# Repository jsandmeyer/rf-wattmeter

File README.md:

## Wattmeter

Based on AK3Y's wattmeter published in QSL magazine.

See license in `main.cpp` for code.  Some other files (like the font) are licensed separately.

### Differences from previous designs
1. Built to run upside-down (heatsink up)
2. Changed to use a Pi Pico 2 to reduce BOM cost
3. Added some built-in standoffs to case
4. Added new holes for USB, and for optional PowerPoles
5. Changed dimensions of PCB and drill/tap locations for heatsink
6. Used 128x64 OLED from AliExpress which did not match datasheet / original dimensions at all
7. Changed microstrip width based on recommendation from calculator
8. I used connectors for everything, but you could just solder the wires in
9. Changed other dimensions of case cutouts
10. Used mostly different parts from original design

### Printing
Try to orient the parts so the smooth side faces out.
1. Print bottom shell normally.
2. The top shell should be rotated 180 degrees for better printing.
3. Front and back panels should be oriented so the "outside" of each plate faces the build plate for a smooth finish.

### Assembly

#### Parts Required

| ID      | Description                   | QTY | Optional QTY |
|---------|-------------------------------|-----|--------------|
| PCB1    | RF PCB                        | 1   |              |
| PCB2    | Pico PCB                      | 1   |              |
| A1      | Raspberry Pi Pico 2           | 1   |              |
| A2      | SSD1306 128x64 I2C OLED       | 1   |              |
| C1      | 10nF 1206 Cer. Cap.           | 1   |              |
| C2      | 1nF 1206 Cer. Cap.            | 1   |              |
| C3      | 10uF 35V 5mm Elec. Cap.       |     | 1            |
| C4      | 47uF 35V 5mm Elec. Cap.       |     | 1            |
| D1-2a,b | TMMBAT41FILM 100V Diode       | 3   |              |
| D3      | PBZTBR13.0B Zener Diode       | 1   |              |
| D4      | 1N5819                        |     | 1            |
| HS1     | 60x45x18mm heatsink           | 1   |              |
| J1      | SMA board-edge connector      | 1   |              |
| J2      | JST-XA BM02B-XASS-TF          | 1   |              |
| J3-4    | JST-XA B02B-XASK-1            | 1   | 1            |
| J5      | 1x4 2.54mm Breakaway Hdr.     | 1   |              |
| R1      | RFR 50-250 Flange Resistor    | 1   |              |
| R2      | 100K 1206 Resistor            | 1   |              |
| R3      | 3K 1206 Resistor              | 1   |              |
| R4      | DNP                           |     |              |
| TH1     | DNP                           |     |              |
| U1      | UA7805                        |     | 1            |
| VR1     | 100K PT10WV05-104A2020-3-NE-S | 1   |              |

#### Cable Assemblies
Cable assemblies assume Pin 1 of a connector is the RIGHTMOST contact if you are looking at the connector's contact end, with the latch facing UP.
Cut wires to the length indicated, then strip and crimp them.

1. 5" Inter-PCB Wire
   1. JST-XA connectors
   2. RF PCB side: Pin 1 is red, Pin 2 is black
   3. Pico PCB side: Pin 1 is black, Pin 2 is red
   4. Pins 1 and 2 are reversed on either board
2. 2.5" PowerPole Wire (optional)
   1. JST-XA connector and PowerPole connector
   2. Pico PCB side: Pin 1 is red, Pin 2 is black
3. 3.5" OLED Wire (DuPont/Molex)
   1. Connectors are symmetrical
   2. Try to use a marked or black conductor for GND

#### Tools Needed
1. Crimping tool for JST & DuPont connectors
2. Crimping tool for PowerPole connectors
3. Drill bits and taps for M2 and M3 screw holes
4. Wire cutters, strippers, pliers
5. Metric allen key / screwdriver / wrench / socket for M2/3 screws and nuts
6. Soldering iron with solder, flux, and solder-wick
7. 3D printer if printing your own case

#### Steps
1. Assemble the heatsink, RF PCB, and flange resistor prior to soldering anything.
   1. Use 4x 6mm M3 screws to hold the PCB to the heatsink
   2. Use 2x 6mm M2 screws to hold the flange resistor to the heatsink
   3. Make sure the flange resistor tab rests on/above the PCB pad for it
2. Soldering the RF PCB
   1. Use flux liberally
   2. The pads for diodes were designed for larger diodes, but many will fit fine
3. Soldering the Pico PCB
   1. Parts U1, C3, C4, D4, and J4 may be omitted if you do not want an external power supply other than USB
   2. D4 is a very tight fit
   3. Use flux to help solder the Pico 2
   4. R4 and Thermistor are optional in case you want to have a Thermistor (you will need to code this in)
4. Installing the PCBs
   1. Insert 4x 8mm M3 screws into the screw holes on the "top" shell from the outside
   2. Place the RF PCB into the "top" shell with the heatsink going through the big hole, and the SMA adapter through the small side hole, aligned with the M3 screws
   3. Attach 4x 15mm~6mm M3 hex standoffs (female side) to the M3 screws to hold the RF PCB down
   4. Attach one end of the inter-PCB wire to the RF PCB
   5. Place the Pico PCB onto the M3 hex standoffs (male side) so that the potentiometer and BOOTSEL button align to the holes when the "bottom" shell is placed onto the "top" shell
   6. Use 4x M3 lock nuts to hold the Pico PCB to the M3 standoffs
   7. Attach the other end of the inter-PCB wire to the Pico PCB
5. Assembling the OLED panel
   1. Mark on the top edge of the OLED panel above the GND pin
   2. Use 4x 8mm M2 screws and M2 lock nuts to hold the OLED display in place on the front panel - be gentle with the PCB
   3. Place the OLED display panel so the connector is above the Pico PCB
   4. Attach the OLED wire between the display and the PCB
6. Assembling the Power/USB panel
   1. Install the PowerPole connector
   2. File the hole for the PowerPole connector if needed
   3. Use glue to secure the PowerPole connector if desired
   4. Place the Power/USB panel so the PowerPole connector is above the Pico PCB
   5. Attach the PowerPole wire to the PCB
7. Assemble the top of the case
   1. Place the "bottom" shell on the assembly
   2. Affix with 4x 6mm M2 screws

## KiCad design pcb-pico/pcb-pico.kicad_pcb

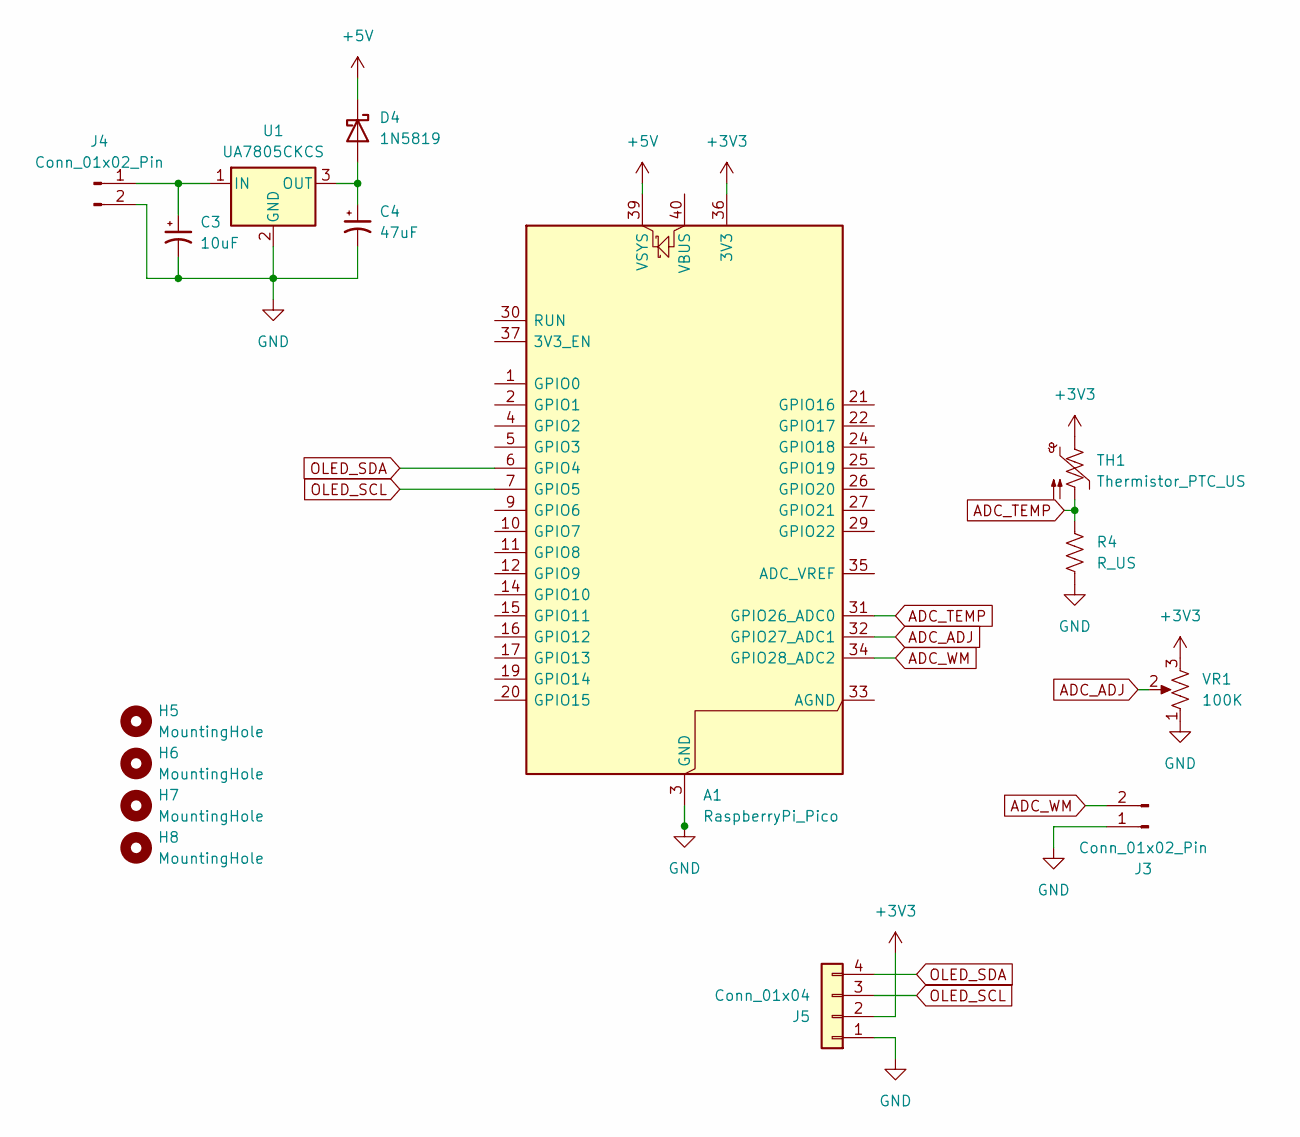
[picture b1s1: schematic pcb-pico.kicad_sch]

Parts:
A1: RaspberryPi_Pico; RaspberryPi_Pico_Common_Unspecified
C3: 10uF; CP_Radial_D5.0mm_P2.00mm
C4: 47uF; CP_Radial_D5.0mm_P2.00mm
D4: 1N5819; D_DO-34_SOD68_P7.62mm_Horizontal
H5, H6, H7, H8: MountingHole; MountingHole_3.2mm_M3
J3, J4: Conn_01x02_Pin; JST_XA_B02B-XASK-1-A_1x02_P2.50mm_Vertical
J5: Conn_01x04; PinHeader_1x04_P2.54mm_Vertical
R4: R_US; R_Axial_DIN0207_L6.3mm_D2.5mm_P10.16mm_Horizontal
TH1: Thermistor_PTC_US; PinHeader_1x02_P2.54mm_Vertical
U1: UA7805CKCS; TO-220-3_Vertical
VR1: 100K; Potentiometer_Piher_PT-10-V05_Vertical

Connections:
+3V3: A1.36 (3V3), J5.2, TH1.1, VR1.3
+5V: A1.39 (VSYS), D4.1 (K)
ADC_ADJ: A1.32 (GPIO27_ADC1), VR1.2
ADC_TEMP: A1.31 (GPIO26_ADC0), R4.1, TH1.2
ADC_WM: A1.34 (GPIO28_ADC2), J3.2
GND: A1.3 (GND), A1.8 (GND), A1.13 (GND), A1.18 (GND), A1.23 (GND), A1.28 (GND), A1.38 (GND), C3.2, C4.2, J3.1, J4.2, J5.1, R4.2, U1.2 (GND), VR1.1
unnamed: C4.1, D4.2 (A), U1.3 (OUT)
unnamed: C3.1, J4.1, U1.1 (IN)
OLED_SCL: A1.7 (GPIO5), J5.3
OLED_SDA: A1.6 (GPIO4), J5.4

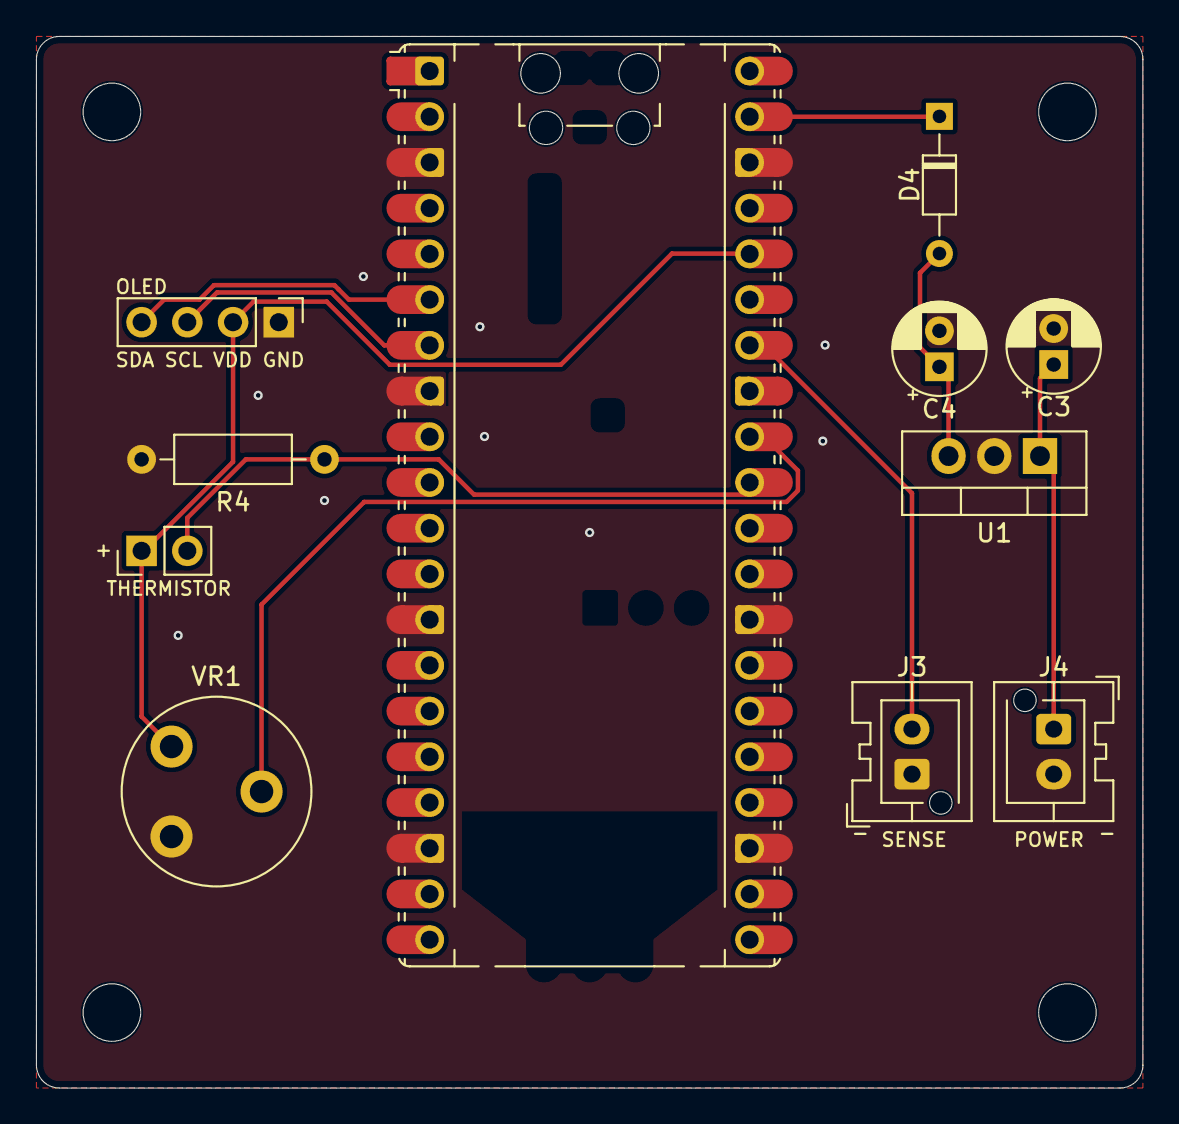
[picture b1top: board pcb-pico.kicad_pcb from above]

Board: 2 copper layers, 61.5 x 58.4 mm, 15 parts (0 on the bottom side), 10 nets.

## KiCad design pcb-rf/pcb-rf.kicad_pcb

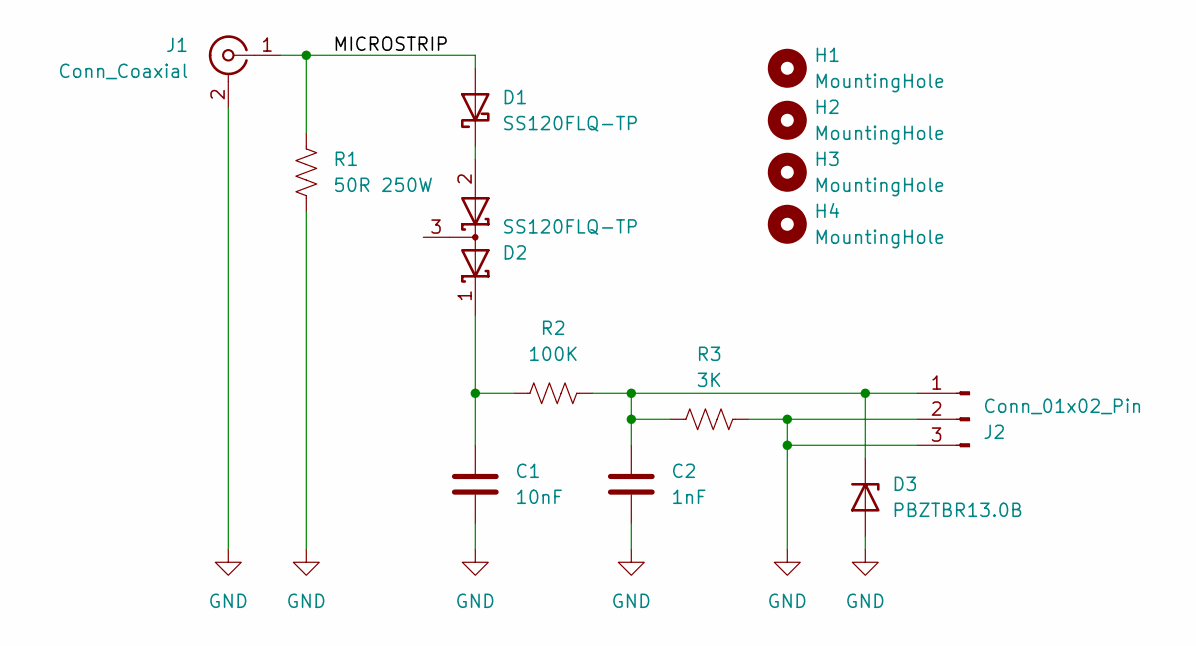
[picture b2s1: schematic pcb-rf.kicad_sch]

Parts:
C1: 10nF; C_1206_3216Metric_Pad1.33x1.80mm_HandSolder
C2: 1nF; C_1206_3216Metric_Pad1.33x1.80mm_HandSolder
D1: SS120FLQ-TP; Vishay_SlimSMA_HV_DO-221AC_HandSolder
D2: SS120FLQ-TP; Vishay_SlimSMA_HV_DO-221AC_HandSolder_SQ
D3: PBZTBR13.0B; D_SMB_Handsoldering
H1, H2, H3, H4: MountingHole; MountingHole_3.2mm_M3
J1: Conn_Coaxial; SMA_Custom_EdgeMount
J2: Conn_01x02_Pin; CONN_BM02B-XASS-TFLFSN_JST
R1: 50R 250W; FlangeResistor
R2: 100K; R_1206_3216Metric_Pad1.30x1.75mm_HandSolder
R3: 3K; R_1206_3216Metric_Pad1.30x1.75mm_HandSolder

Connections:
/MICROSTRIP: D1.2 (A), J1.1 (In), R1.1
GND: C1.2, C2.2, D3.2 (A), J1.2 (Ext), J2.2, J2.3, R1.2, R3.1
unnamed: D1.1 (K), D2.2 (A)
unnamed: C1.1, D2.1 (K), R2.2
unnamed: C2.1, D3.1 (K), J2.1, R2.1, R3.2

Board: 2 copper layers, 14 parts (0 on the bottom side), 5 nets, no tracks yet.

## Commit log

2025-06-20 update docs
